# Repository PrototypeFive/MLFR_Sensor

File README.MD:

# MLFR_Sensor 
## (Micro_Laser_Filament_Runout_Sensor)

MLFR_Sensor is 3D printer filament runout sensor based on VCNT2030 Reflective Optical sensor.\
It uses microscopic IR laser and a phototransistor to detect transparent and less reflective materials.

**Supply voltage:** 5V

**Logic:** Active Low

### Print the enclosure:
Use 0.2mm layer height, 2-3 perimeters and 30% infill.<br/>
Print enclosure base with black PLA or PETG.<br/>
Position vertical, like on image. It's important, because the geometry inside diffuses the laser.<br/>
There is a sacrifical layer to be removed.<br/>
Print cover with transparent PLA or PETG, position flat on bed.<br/> 

License: CERN-OHL-S version 2

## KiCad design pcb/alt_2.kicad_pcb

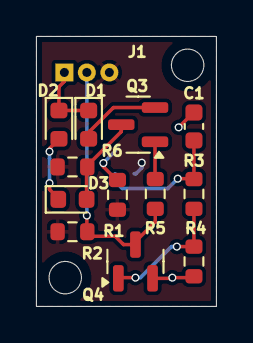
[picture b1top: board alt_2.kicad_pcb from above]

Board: 2 copper layers, 10.0 x 15.0 mm, 14 parts (1 on the bottom side), 10 nets.

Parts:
C1: 22uF; C_0603_1608Metric
D1: LED_R; LED_0603_1608Metric
D2: LED_G; LED_0603_1608Metric
D3: TS4148; D_0603_1608Metric
J1: Conn_01x03_Pin; Conn_3p_1.25mm
Q3, Q4: BC847; SOT-23
R1: 560; R_0603_1608Metric
R2: 1k; R_0603_1608Metric
R3, R5: 10k; R_0603_1608Metric
R4: 4.7k; R_0603_1608Metric
R6: 330; R_0603_1608Metric
VCNT1: vcnt2030

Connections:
+5V: J1.3, R1.2, R2.1, R6.1, VCNT1.4 (Collector)
EMIT: C1.2, R3.1, VCNT1.1 (Emitter)
GND: C1.1, D1.1 (K), D2.1 (K), J1.1, Q4.2 (E), R4.2, VCNT1.3 (VCSEL_C)
unnamed: D1.2 (A), Q3.2 (E)
unnamed: D2.2 (A), D3.1 (K)
unnamed: D3.2 (A), Q3.3 (C), R6.2
unnamed: Q3.1 (B), R5.2
unnamed: Q4.1 (B), R3.2, R4.1
unnamed: R1.1, VCNT1.2 (VCSEL_A)
OUT: J1.2, Q4.3 (C), R2.2, R5.1

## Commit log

2026-01-30 edit readme.md

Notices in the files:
pcb/alt_2.kicad_pcb:
CERN-OHL-S-2.0
